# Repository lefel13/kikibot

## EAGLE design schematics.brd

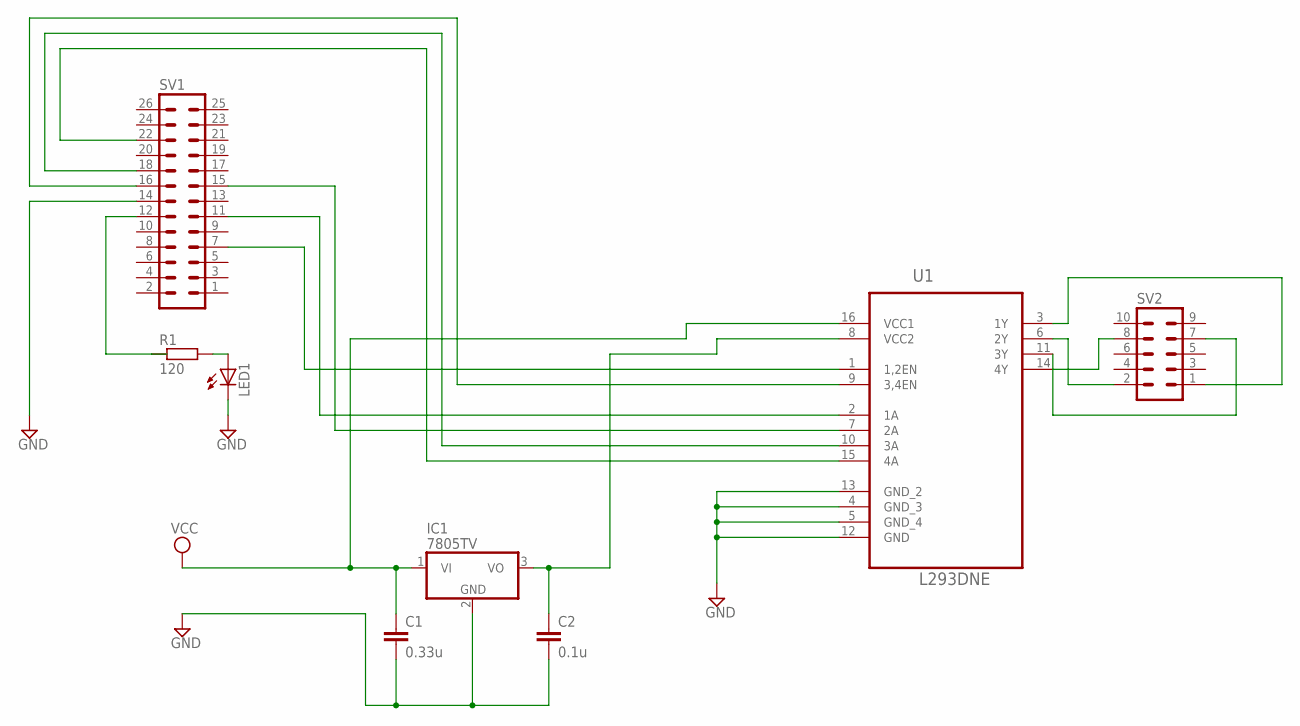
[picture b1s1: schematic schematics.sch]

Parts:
C1: 0.33u; C025-025X050
C2: 0.1u; C025-025X050
IC1: 7805TV; TO220V
LED1: LED5MM
R1: 120; 0207/10
SV1: MA13-2
SV2: MA05-2
U1: L293DNE; DIP254P762X508-16

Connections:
GND: C1.2, C2.2, IC1.2 (GND), LED1.K (C), SV1.14, U1.4 (GND_3), U1.5 (GND_4), U1.12 (GND), U1.13 (GND_2)
unnamed: SV1.7, U1.1 (1,2EN)
unnamed: C2.1, IC1.3 (VO), U1.8 (VCC2)
unnamed: SV1.11, U1.2 (1A)
unnamed: LED1.A, R1.2
unnamed: SV1.15, U1.7 (2A)
unnamed: SV1.16, U1.9 (3,4EN)
unnamed: SV1.18, U1.10 (3A)
unnamed: SV1.22, U1.15 (4A)
unnamed: SV2.1, U1.3 (1Y)
unnamed: SV2.2, U1.6 (2Y)
unnamed: SV2.8, U1.14 (4Y)
unnamed: SV2.7, U1.11 (3Y)
unnamed: R1.1, SV1.12
VCC: C1.1, IC1.1 (VI), U1.16 (VCC1)

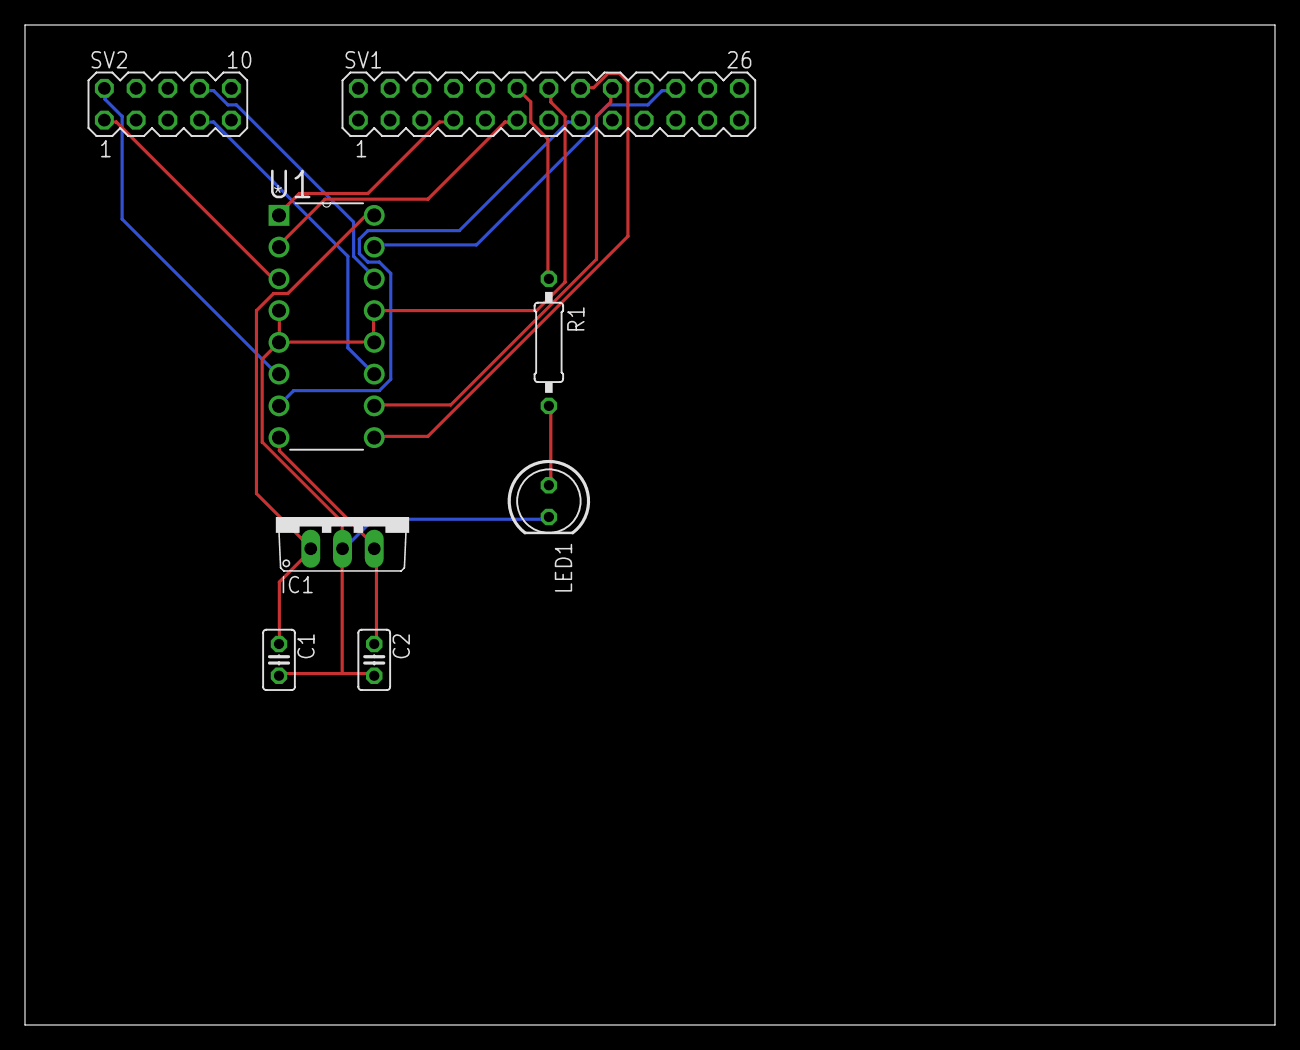
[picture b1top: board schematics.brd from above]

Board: 2 copper layers, 100.0 x 80.0 mm, 8 parts (0 on the bottom side), 15 nets.

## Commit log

2016-11-08 Init branche integration
2016-11-08 Init branche developpement materiel
2016-11-08 Init branche developpement logiciel embarqué
2016-11-08 Init branche developpement logiciel utilisateur
2016-11-08 1er commit => insulte
    je vous traîte de cono ! reste à valider
2016-11-08 boobs
    boooobs
2016-11-09 Ajout des fichiers de CAO pour l'électronique de commande des moteurs
    Fichiers Eagle CAD
    Routage du PCB à revoir
2016-11-09 Initialisation des fichiers pour la librairie de commande des moteurs
2016-11-13 Mise en place de l'environnement de compilation pour une librairie partagée
    Validé avec un code minimal (Hello World)
2016-11-14 Premier code pour utilisation de la librairie GPIO en c "wiringPi"
    Validé !
2017-01-08 AJout des en-tête compatibles doxygen
2017-01-08 Codage librairie moteurs
    Ecriture des prototypes, codage de la fonction d'initialisation. Code
    non compilé, non validé.
2017-01-09 Fin du codage de la librairie de pilotage moteurs
    Code compilé, à tester
2017-01-09 Suppression tabulation à la fin du Makefile
2017-01-09 MAJ programme de test
    Programme de test codé et compilé. Restant à faire : câbler le robot /
    mettre àjour les numéros de pins / recompiler la librairie / tester
2017-01-09 petit essai maitrisé
2017-01-10 MAJ fichier .epf suite à MAJ Eagle CAD en v7.7.0
    (Ancienne version eagle CAD 7.5.0
2017-01-10 MAJ des numéros de pin selon schéma électrique
2017-01-10 Corrections sur le programme de test
2017-01-10 Essai avec numéros de broches de wiringPi
    Les premiers essais ont été faits avec les numéo de broches de P1
    (utilisation de wiringPiSetupPhys à l'init)
    Cela n'a pas fonctionné
    Dans ce commit la lib a été modifié pour utilisation des numéros de
    broches de la lib wiringPi (utilisation de wiringPiSetup à l'init) mais
    cela a eu le même effet
2017-01-16 Début d'écriture d'un programme outillage d'identification des pins GPIO par la librairie wiringPi
2017-01-17 Fin du codage du programme outillage pour identifier les numéros de pin de wringPi
2017-06-25 Creation d'un programme outillage pour tester PWM
2017-06-25 Modification de la lib pour utilisation du PWM SW
    A tester
